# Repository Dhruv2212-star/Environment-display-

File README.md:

**The project is divided into 8 major parts**  
lets understand each component's function one by one in a block to see what function they have in the circuit.   
1. Block 1 – USB Input & Protection  

| Ref | Component        | Role in the Circuit                                                                     |
| --- | ---------------- | --------------------------------------------------------------------------------------- |
| J1  | USB-C Receptacle | Receives 5 V power and USB data from the host PC.                                       |
| D1  | TVS Diode        | Protects the board from ESD and voltage spikes coming through the USB connector.        |
| F1  | Polyfuse         | Limits current during short circuits and protects the USB port from overcurrent damage. |
| R1  | 5.1 kΩ           | USB-C CC1 pull-down resistor to advertise the board as a power sink.                    |
| R2  | 5.1 kΩ           | USB-C CC2 pull-down resistor to advertise the board as a power sink.                    |

2. Block 2 – 3.3 V Power Supply

| Ref | Component       | Role in the Circuit                                                                 |
| --- | --------------- | ----------------------------------------------------------------------------------- |
| U1  | TPS62162        | Converts the USB 5 V input into a stable 3.3 V supply with high efficiency.         |
| L1  | 2.2 µH Inductor | Stores energy during switching and smooths the regulator output current.            |
| C1  | 10 µF           | Input bulk capacitor that stabilizes the 5 V input to the regulator.                |
| C2  | 100 nF          | High-frequency input bypass capacitor that filters switching noise.                 |
| C4  | 4.7 µF          | Main output capacitor that stabilizes the 3.3 V output voltage.                     |
| C9  | 100 µF          | Bulk output capacitor that supplies transient current to the ESP32 and peripherals. |
| R3  | 100 kΩ          | Feedback resistor used by the regulator to maintain the correct output voltage.     |

3. Block 3 – USB to UART Interface  

| Ref | Component | Role in the Circuit                                                                           |
| --- | --------- | --------------------------------------------------------------------------------------------- |
| U2  | CP2102N   | Converts USB communication into UART for programming and serial communication with the ESP32. |
| C3  | 100 nF    | Decouples the CP2102N supply to reduce high-frequency noise.                                  |
| C5  | 1 µF      | Stabilizes the USB VBUS supply for the CP2102N.                                               |
| C6  | 1 µF      | Stabilizes the internal regulator output of the CP2102N.                                      |

4. Block 4 – ESP32 Auto-Programming Circuit  

| Ref | Component   | Role in the Circuit                                                        |
| --- | ----------- | -------------------------------------------------------------------------- |
| Q1  | MMBT3904    | Uses the RTS signal to automatically reset the ESP32.                      |
| Q2  | MMBT3904    | Uses the DTR signal to place the ESP32 into bootloader mode automatically. |
| R11 | 10 kΩ       | Pull-up resistor for the ESP32 EN pin.                                     |
| R12 | 10 kΩ       | Pull-up resistor for the ESP32 GPIO0 (BOOT) pin.                           |
| SW1 | Push Button | Manual reset button for the ESP32.                                         |
| SW2 | Push Button | Manual bootloader button for programming mode.                             |

5. Block 5 – ESP32 Module  

| Ref | Component       | Role in the Circuit                                                                                          |
| --- | --------------- | ------------------------------------------------------------------------------------------------------------ |
| U3  | ESP32-WROOM-32E | Main microcontroller that reads sensors, stores data, communicates over USB, and controls the entire system. |
| C10 | 100 nF          | Local decoupling capacitor placed close to the ESP32 power pin.                                              |
| C11 | 100 nF          | Additional high-frequency decoupling capacitor for stable ESP32 operation.                                   |
| C16 | 10 µF           | Bulk capacitor that supports sudden current demands from the ESP32's Wi-Fi and Bluetooth radio.              |

6.  Block 6 – Environmental Sensors

(a) BME280  

| Ref | Component | Role in the Circuit                                       |
| --- | --------- | --------------------------------------------------------- |
| U4  | BME280    | Measures temperature, humidity, and atmospheric pressure. |
| C12 | 100 nF    | Filters supply noise to improve sensor accuracy.          |

(b)  BH1750  

| Ref | Component | Role in the Circuit                                       |
| --- | --------- | --------------------------------------------------------- |
| U4  | BME280    | Measures temperature, humidity, and atmospheric pressure. |
| C12 | 100 nF    | Filters supply noise to improve sensor accuracy.          |

(c) RTC  

| Ref | Component      | Role in the Circuit                                               |
| --- | -------------- | ----------------------------------------------------------------- |
| U6  | DS3231M        | Maintains accurate date and time, even when USB power is removed. |
| BT1 | CR2032 Battery | Keeps the RTC running during power loss.                          |
| C15 | 100 nF         | Decouples the RTC power supply.                                   |

7. Block 7 – microSD Storage  

| Ref | Component        | Role in the Circuit                                                           |
| --- | ---------------- | ----------------------------------------------------------------------------- |
| J3  | MicroSD Socket   | Stores logged environmental data on a removable SD card.                      |
| R9  | Pull-up resistor | Pulls the Card Detect line to a defined logic level when no card is inserted. |

8. Block 8 – User Interface

| Ref | Component   | Role in the Circuit                                                         |
| --- | ----------- | --------------------------------------------------------------------------- |
| J2  | OLED Header | Connects the external OLED display over the I²C bus.                        |
| D2  | Status LED  | Indicates board status such as power or firmware activity.                  |
| R10 | 1 kΩ        | Limits current through the status LED to protect it from excessive current. |

# Schematic 

# Final traced PCB 

# 3D view of the assumed PCB look

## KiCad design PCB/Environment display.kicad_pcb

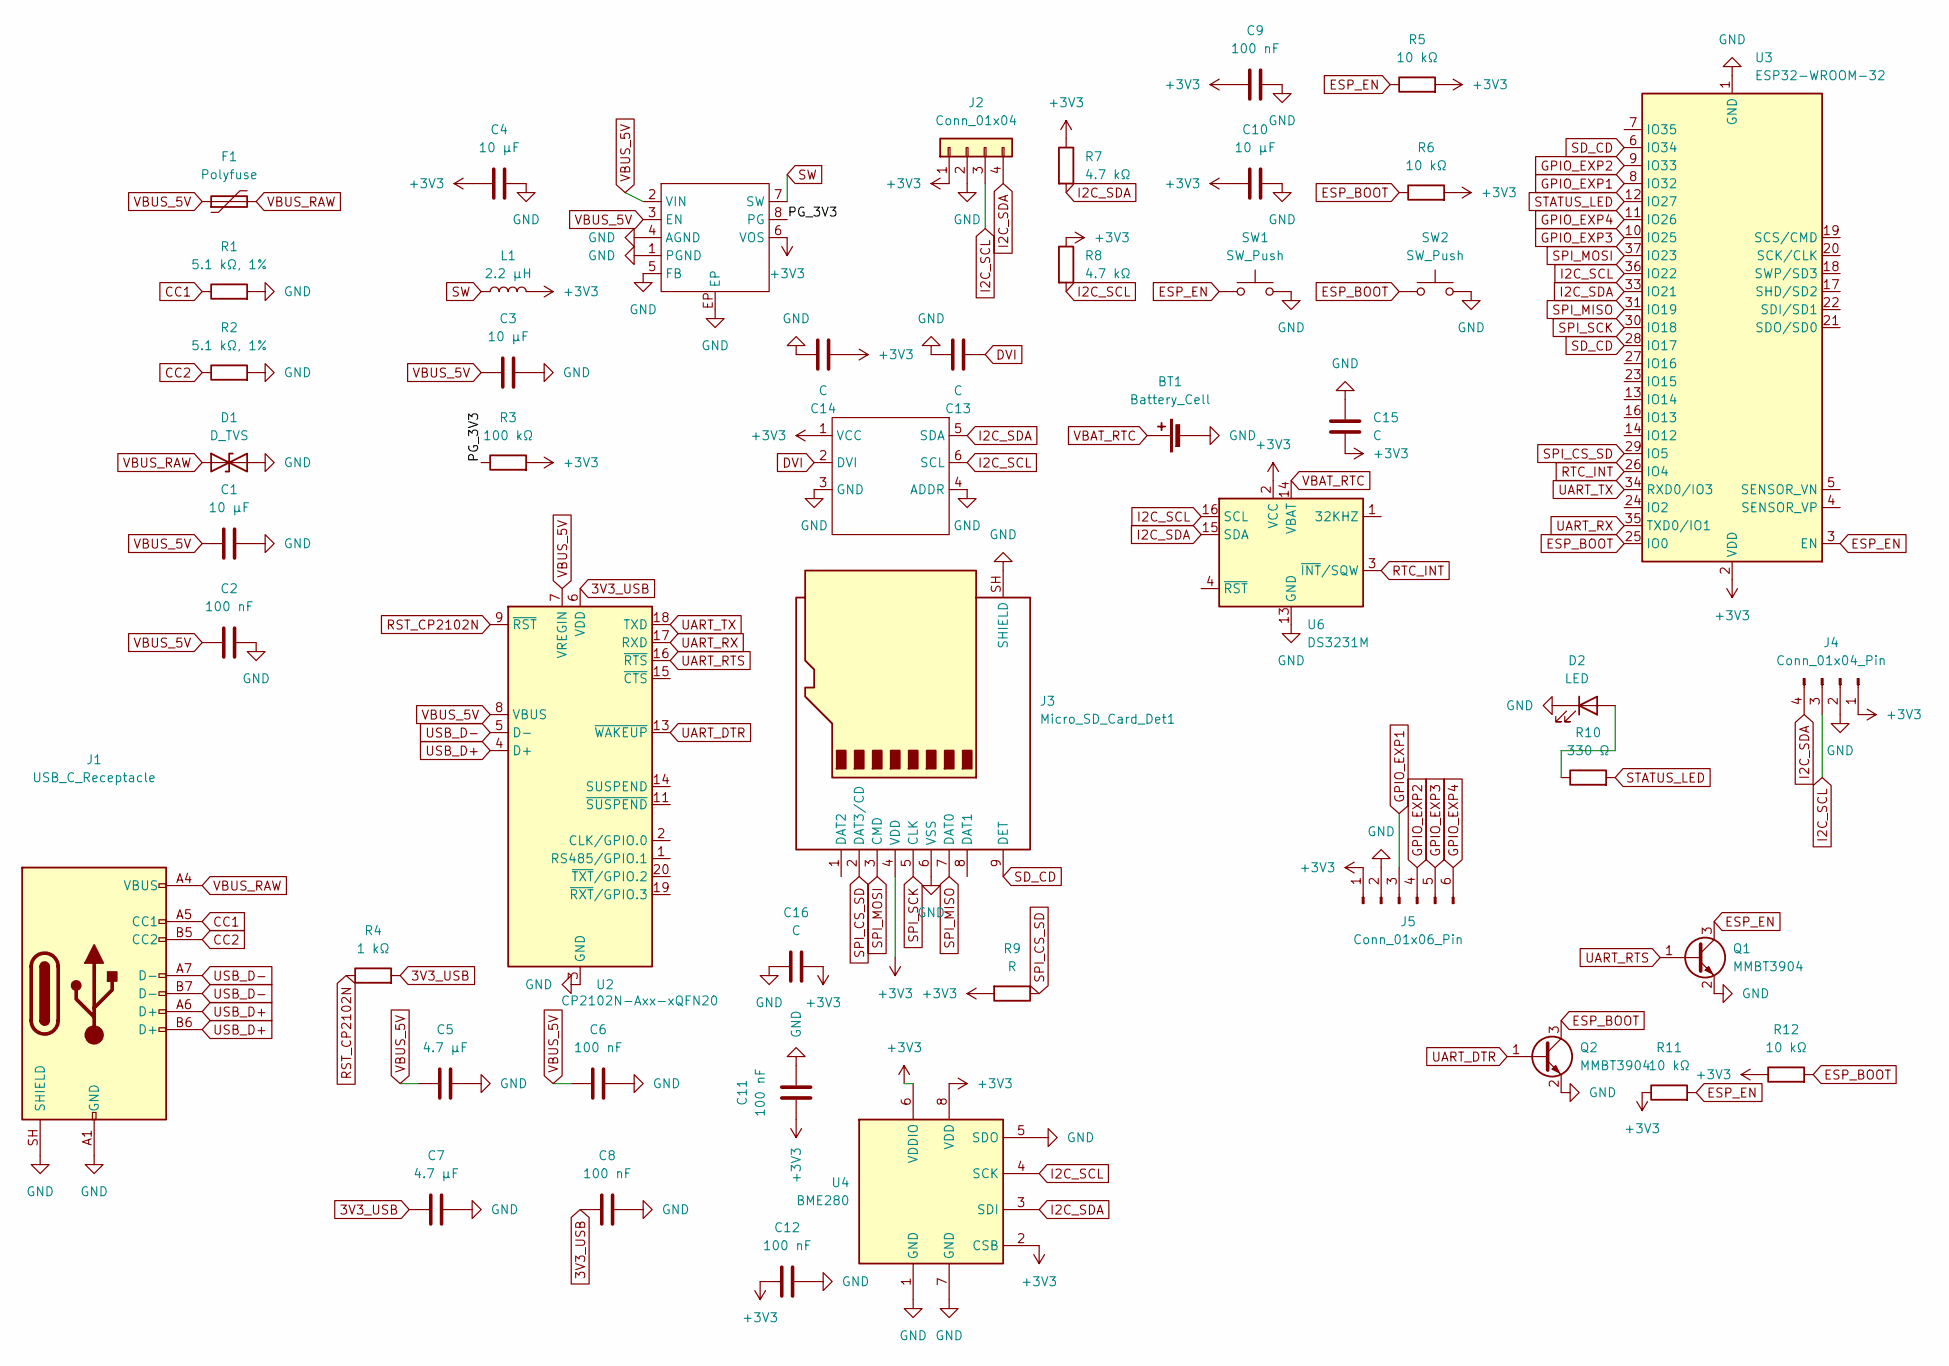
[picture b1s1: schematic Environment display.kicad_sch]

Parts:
BT1: Battery_Cell; BatteryHolder_Keystone_1060_1x2032
C1, C3, C4, C10: 10 µF; C_0805_2012Metric
C2, C6, C8, C9, C11, C12: 100 nF; C_0603_1608Metric
C5, C7: 4.7 µF; C_0805_2012Metric
C13, C14: C; C_0805_2012Metric
C15, C16: C; C_0603_1608Metric
D1: D_TVS; SOT-23-3
D2: LED; LED_0603_1608Metric
F1: Polyfuse; Fuse_1206_3216Metric
J1: USB_C_Receptacle; USB_C_Receptacle_HRO_TYPE-C-31-M-12
J2: Conn_01x04; PinHeader_1x04_P2.54mm_Vertical
J3: Micro_SD_Card_Det1; MOLEX_104031-0811
J4: Conn_01x04_Pin; PinHeader_1x04_P2.54mm_Vertical
J5: Conn_01x06_Pin; PinHeader_1x06_P2.54mm_Vertical
L1: 2.2 µH; MURATA_LQH44PN2R2MPRL
Q1, Q2: MMBT3904; SOT-23
R1, R2: 5.1 kΩ, 1%; R_0603_1608Metric
R3: 100 kΩ; R_0603_1608Metric
R4: 1 kΩ; R_0603_1608Metric
R5, R6, R11, R12: 10 kΩ; R_0603_1608Metric
R7, R8: 4.7 kΩ; R_0603_1608Metric
R9: R; R_0603_1608Metric
R10: 330 Ω; R_0603_1608Metric
SW1, SW2: SW_Push; SW_SPST_SKQG_WithoutStem
U1: DSG0008A
U2: CP2102N-Axx-xQFN20; QFN-20-1EP_3x3mm_P0.4mm_EP1.65x1.65mm
U3: ESP32-WROOM-32
U4: BME280; Bosch_LGA-8_2.5x2.5mm_P0.65mm_ClockwisePinNumbering
U5: XDCR_BH1750FVI-TR
U6: DS3231M; SOIC-16W_7.5x10.3mm_P1.27mm

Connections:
3V3_USB: C7.1, C8.1, R4.2, U2.6 (VDD)
+3V3: C4.1, C9.1, C10.1, C11.1, C12.1, C14.1, C15.1, C16.1, J2.1, J3.4 (VDD), J4.1, J5.1, L1.2, R3.2, R5.2, R6.2, R7.1, R8.1, R9.2, R11.1, R12.1, U1.6 (VOS), U3.2 (VDD), U4.2 (CSB), U4.6 (VDDIO), U4.8 (VDD), U5.1 (VCC), U6.2 (VCC)
/PG_3V3: R3.1, U1.8 (PG)
CC1: J1.A5 (CC1), R1.1
CC2: J1.B5 (CC2), R2.1
DVI: C13.1, U5.2 (DVI)
ESP_BOOT: Q2.3 (C), R6.1, R12.2, SW2.1, U3.25 (IO0)
ESP_EN: Q1.3 (C), R5.1, R11.2, SW1.1, U3.3 (EN)
GND: BT1.2 (-), C1.2, C2.2, C3.2, C4.2, C5.2, C6.2, C7.2, C8.2, C9.2, C10.2, C11.2, C12.2, C13.2, C14.2, C15.2, C16.2, D1.2 (A2), D2.1 (K), J1.A1 (GND), J1.A12 (GND), J1.B1 (GND), J1.B12 (GND), J1.SH (SHIELD), J2.2, J3.6 (VSS), J3.SH (SHIELD), J4.2, J5.2, Q1.2 (E), Q2.2 (E), R1.2, R2.2, SW1.2, SW2.2, U1.1 (PGND), U1.4 (AGND), U1.5 (FB), U1.EP, U2.3 (GND), U2.12 (GND), U2.21 (GND), U3.1 (GND), U3.15 (GND), U3.38 (GND), U3.39 (GND), U4.1 (GND), U4.5 (SDO), U4.7 (GND), U5.3 (GND), U5.4 (ADDR), U6.5 (GND), U6.6 (GND), U6.7 (GND), U6.8 (GND), U6.9 (GND), U6.10 (GND), U6.11 (GND), U6.12 (GND), U6.13 (GND)
GPIO_EXP1: J5.3, U3.8 (IO32)
GPIO_EXP2: J5.4, U3.9 (IO33)
GPIO_EXP3: J5.5, U3.10 (IO25)
GPIO_EXP4: J5.6, U3.11 (IO26)
I2C_SCL: J2.3, J4.3, R8.2, U3.36 (IO22), U4.4 (SCK), U5.6 (SCL), U6.16 (SCL)
I2C_SDA: J2.4, J4.4, R7.2, U3.33 (IO21), U4.3 (SDI), U5.5 (SDA), U6.15 (SDA)
unnamed: D2.2 (A), R10.1
RST_CP2102N: R4.1, U2.9 (~RST)
RTC_INT: U3.26 (IO4), U6.3 (~INT/SQW)
SD_CD: J3.9 (DET), U3.6 (IO34), U3.28 (IO17)
SPI_CS_SD: J3.2 (DAT3/CD), R9.1, U3.29 (IO5)
SPI_MISO: J3.7 (DAT0), U3.31 (IO19)
SPI_MOSI: J3.3 (CMD), U3.37 (IO23)
SPI_SCK: J3.5 (CLK), U3.30 (IO18)
STATUS_LED: R10.2, U3.12 (IO27)
SW: L1.1, U1.7 (SW)
UART_DTR: Q2.1 (B), U2.13 (~WAKEUP)
UART_RTS: Q1.1 (B), U2.16 (~RTS)
UART_RX: U2.17 (RXD), U3.35 (TXD0/IO1)
UART_TX: U2.18 (TXD), U3.34 (RXD0/IO3)
USB_D+: J1.A6 (D+), J1.B6 (D+), U2.4 (D+)
USB_D−: J1.A7 (D-), J1.B7 (D-), U2.5 (D-)
VBAT_RTC: BT1.1 (+), U6.14 (VBAT)
VBUS_5V: C1.1, C2.1, C3.1, C5.1, C6.1, F1.1, U1.2 (VIN), U1.3 (EN), U2.7 (VREGIN), U2.8 (VBUS)
VBUS_RAW: D1.1 (A1), F1.2, J1.A4 (VBUS), J1.A9 (VBUS), J1.B4 (VBUS), J1.B9 (VBUS)

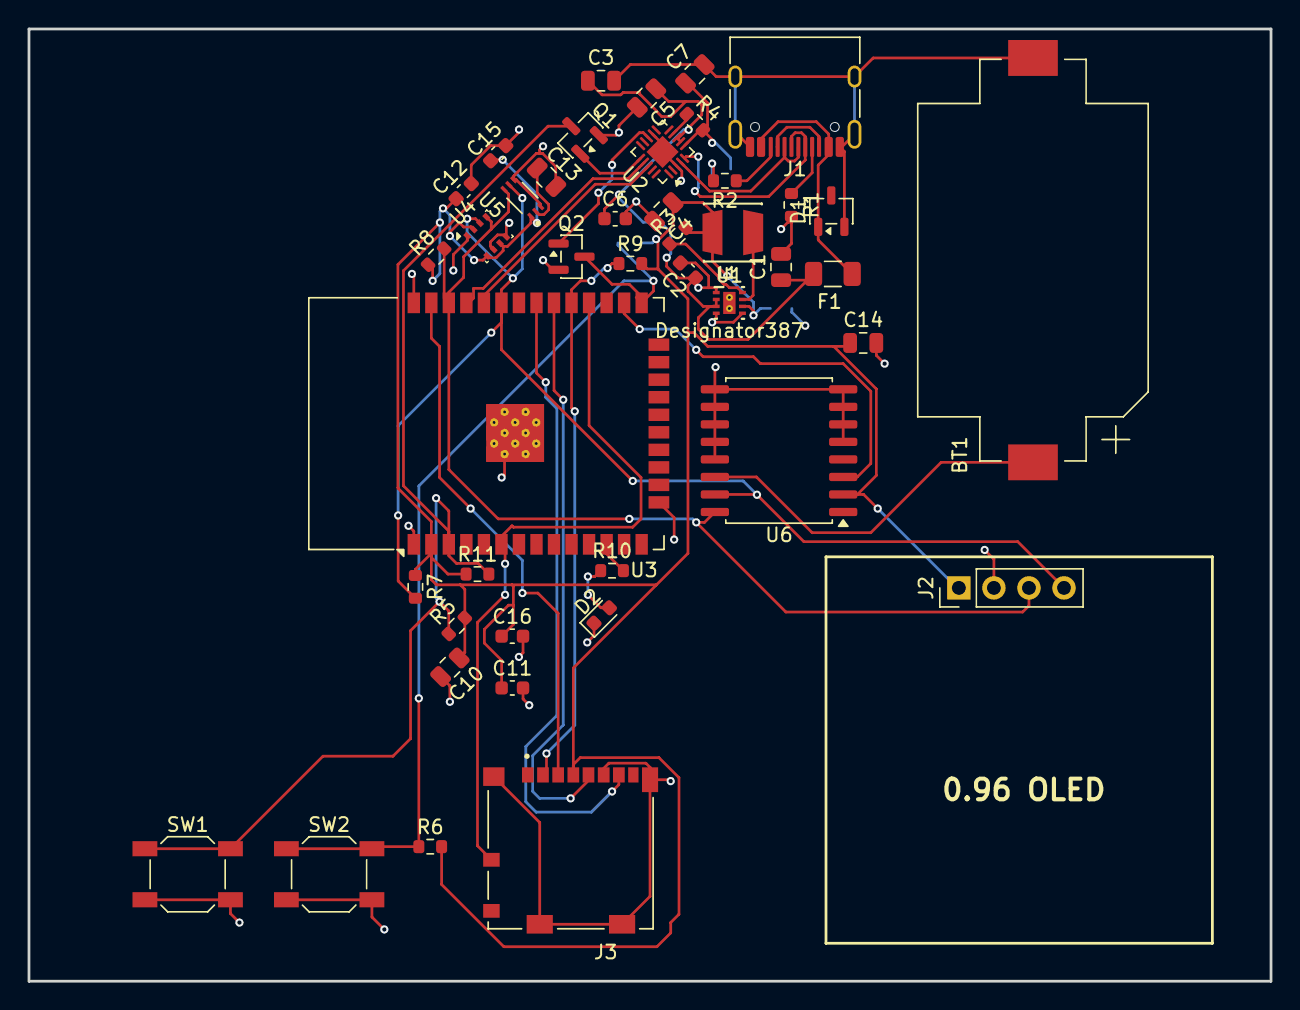
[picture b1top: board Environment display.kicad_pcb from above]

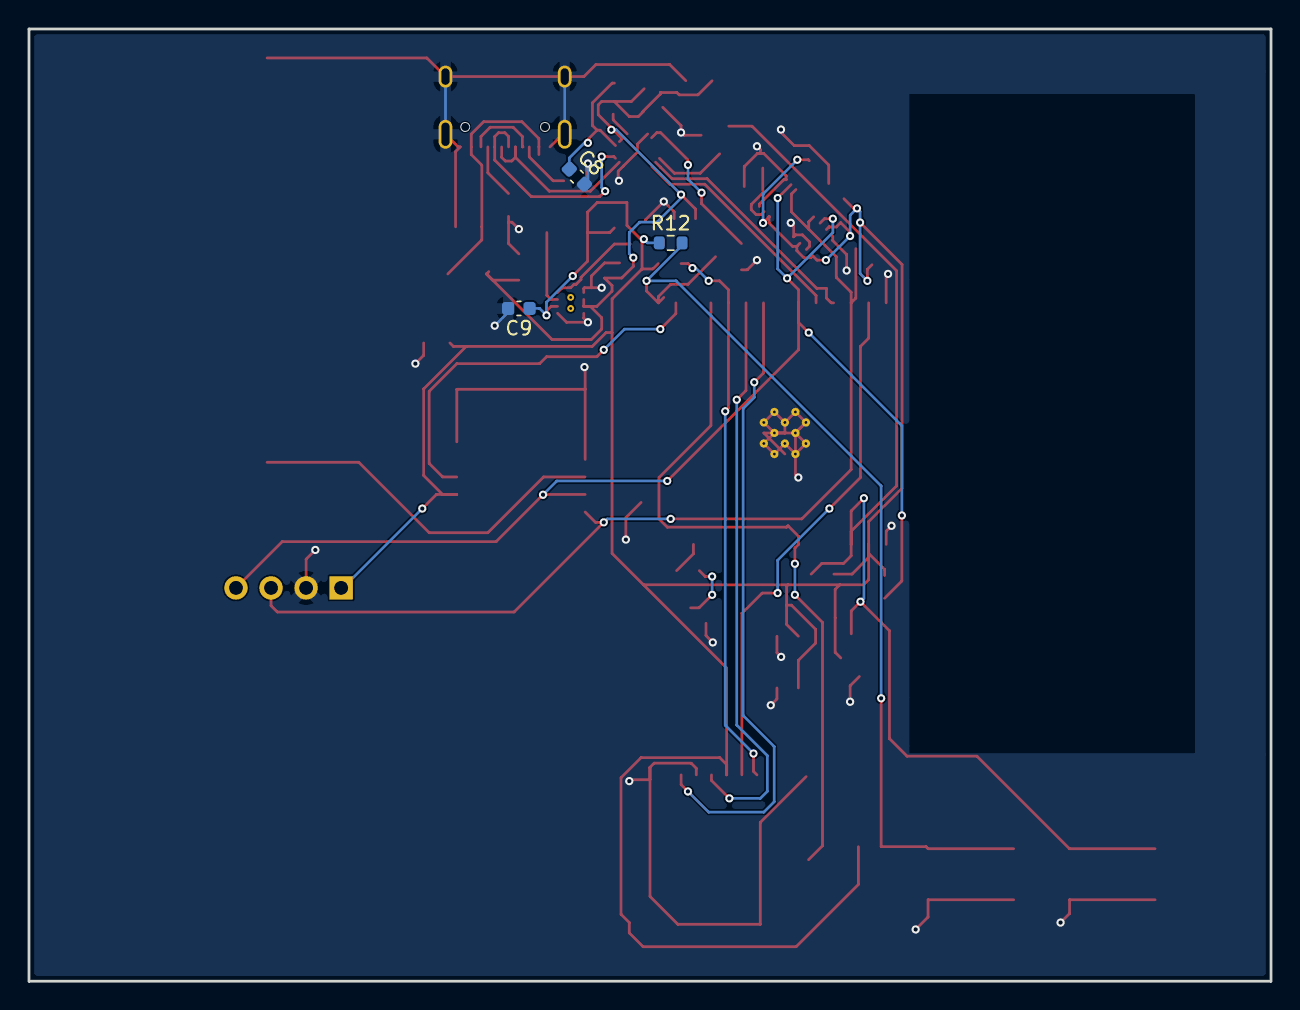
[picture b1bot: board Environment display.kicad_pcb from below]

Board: 2 copper layers, 90.0 x 69.0 mm, 46 parts (3 on the bottom side), 30 nets.
